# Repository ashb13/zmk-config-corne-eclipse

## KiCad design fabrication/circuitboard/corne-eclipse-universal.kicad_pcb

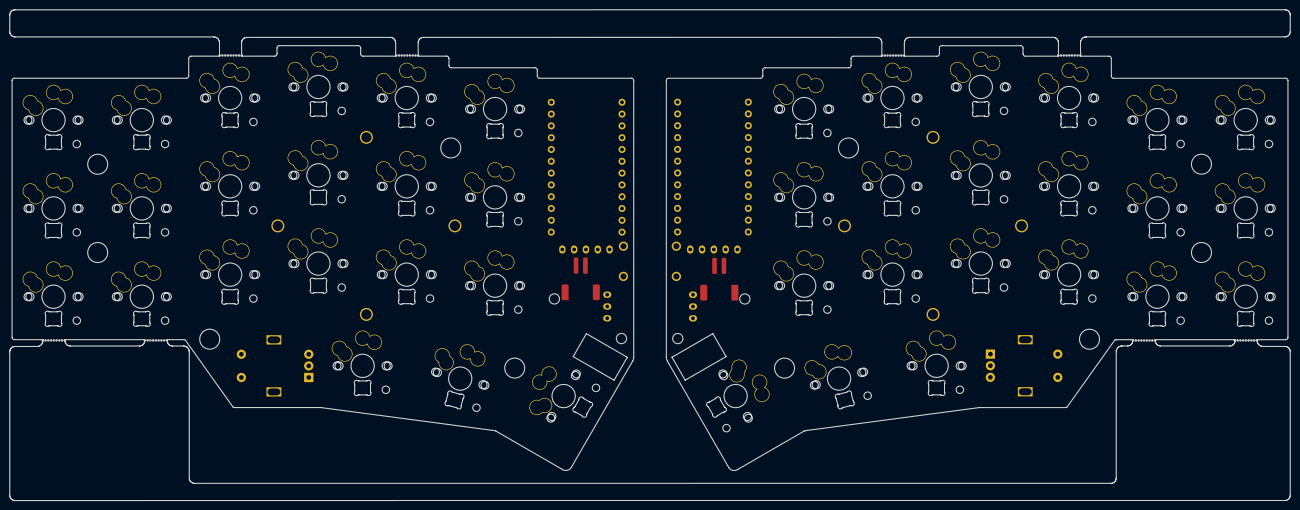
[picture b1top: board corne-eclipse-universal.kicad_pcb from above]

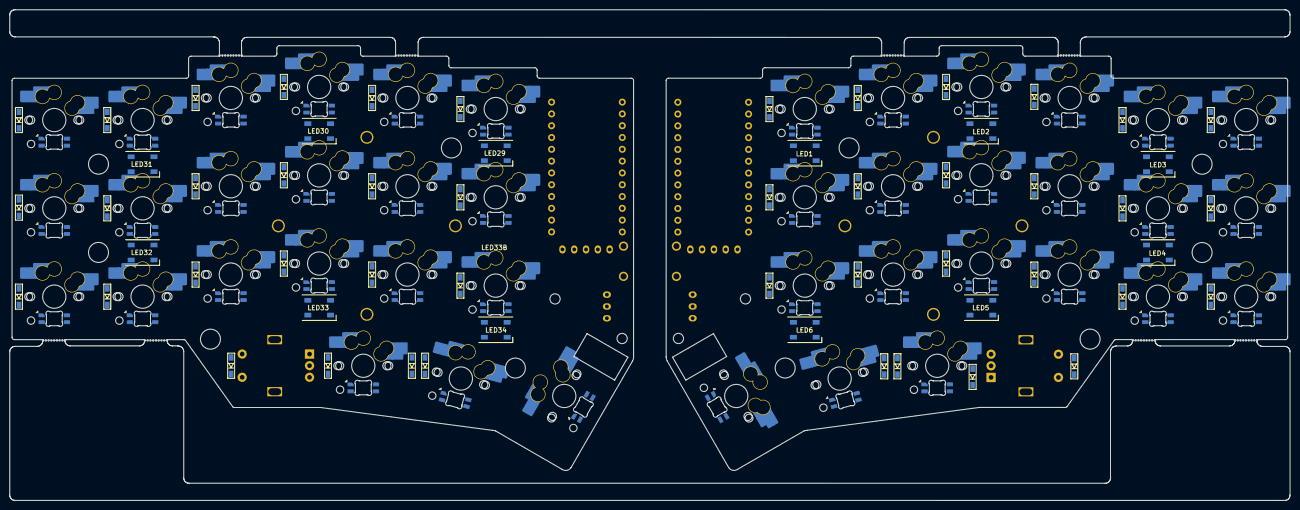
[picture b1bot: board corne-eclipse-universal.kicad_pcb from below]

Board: 2 copper layers, 275.5 x 105.6 mm, 178 parts (105 on the bottom side), 131 nets, no tracks yet.

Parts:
BT1, BT2, BT3, BT4, BT5, BT6, BT7, BT8: Breakaway_Tabs
D1, D2, D3, D4, D5, D6, D7, D8, D9, D10, D11, D12, D13, D14, D15, D16, D17, D18, D19, D19B, D20, D21, D22, D23, D24, D25, D26, D27, D28, D29, D30, D31, D32, D33, D34, D35, D36, D37, D38, D39, D40, D40B, D41, D42: D; D3_SMD_v2
ENC1, ENC2: RotaryEncoder_Alps_EC11E-Switch_Vertical_H20mm
J2, J4: OLED; nice!view
JPT1, JPT2: JST Passthrough
JST1, JST2: JST_PH_S2B-PH-SM4-TB_1x02-1MP_P2.00mm_Horizontal
LED1, LED2, LED3, LED4, LED5, LED6, LED29, LED30, LED31, LED32, LED33, LED33B: WS2812B; LED_WS2812B_PLCC4_5.0x5.0mm_P3.2mm
LED7, LED8, LED9, LED10, LED11, LED12, LED13, LED14, LED15, LED16, LED17, LED18, LED19, LED20, LED21, LED23, LED24, LED25, LED26, LED27, LED28, LED35, LED36, LED37, LED38, LED39, LED40, LED41, LED42, LED43, LED44, LED45, LED46, LED47, LED48, LED49, LED51, LED52, LED53, LED54, LED55, LED56: LED_6028R; LED_choc_6028R
MH1, MH2, MH3, MH4, MH5, MH6, MH7, MH8, MH9, MH10, MH11, MH12, MH13, MH14: Val**; M2_HOLE_v2
PWR1, PWR2: power
RSW1, RSW2: SW_PUSH; ResetSW_1side
SW1, SW2, SW3, SW4, SW5, SW6, SW7, SW8, SW9, SW10, SW11, SW12, SW13, SW14, SW15, SW16, SW17, SW18, SW20, SW21, SW23, SW24, SW25, SW26, SW27, SW28, SW29, SW30, SW31, SW32, SW33, SW34, SW35, SW36, SW37, SW38, SW39, SW40, SW42, SW43: SW_Universal_HS; SW_Universal_HS_1u
SW22, SW44: SW_Universal_HS; SW_Universal_HS_1.5u
TP1, TP2: Tenting Puck; Tenting_Puck
U1, U2: nice!nano; ProMicro_v3

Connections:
GND: ENC1.C, J2.4, LED1.3, LED2.3, LED3.3, LED4.3, LED5.3, LED6.3, LED7.2, LED8.2, LED9.2, LED10.2, LED11.2, LED12.2, LED13.2, LED14.2, LED15.2, LED16.2, LED17.2, LED18.2, LED19.2, LED20.2, LED21.2, LED23.2, LED24.2, LED25.2, LED26.2, LED27.2, LED28.2, U1.3, U1.4, U1.23
GNDA: ENC2.C, J4.4, LED29.3, LED30.3, LED31.3, LED32.3, LED33.3, LED33B.3, LED35.2, LED36.2, LED37.2, LED38.2, LED39.2, LED40.2, LED41.2, LED42.2, LED43.2, LED44.2, LED45.2, LED46.2, LED47.2, LED48.2, LED49.2, LED51.2, LED52.2, LED53.2, LED54.2, LED55.2, LED56.2, U2.3, U2.4, U2.23
LED_r: LED29.prev, U2.1
unnamed: D1.2, SW1.2
unnamed: D2.2, SW2.2
unnamed: D3.2, SW3.2
unnamed: D4.2, SW4.2
unnamed: D5.2, SW5.2
unnamed: D6.2, SW6.2
unnamed: D7.2, SW7.2
unnamed: D8.2, SW8.2
unnamed: D9.2, SW9.2
unnamed: D10.2, SW10.2
unnamed: D11.2, SW11.2
unnamed: D12.2, SW12.2
unnamed: D13.2, SW13.2
unnamed: D14.2, SW14.2
unnamed: D15.2, SW15.2
unnamed: D16.2, SW16.2
unnamed: D17.2, SW17.2
unnamed: D18.2, SW18.2
unnamed: D19B.2, ENC1.S1
unnamed: D19.2, SW20.2
unnamed: D20.2, SW21.2
unnamed: D21.2, SW22.2
unnamed: D22.2, SW23.2
unnamed: D23.2, SW24.2
unnamed: D24.2, SW25.2
unnamed: D25.2, SW26.2
unnamed: D26.2, SW27.2
unnamed: D27.2, SW28.2
unnamed: D28.2, SW29.2
unnamed: D29.2, SW30.2
unnamed: D30.2, SW31.2
unnamed: D31.2, SW32.2
unnamed: D32.2, SW33.2
unnamed: D33.2, SW34.2
unnamed: D34.2, SW35.2
unnamed: D35.2, SW36.2
unnamed: D36.2, SW37.2
unnamed: D37.2, SW38.2
unnamed: D38.2, SW39.2
unnamed: D39.2, SW40.2
unnamed: D40B.2, ENC2.S1
unnamed: D40.2, SW42.2
unnamed: D41.2, SW43.2
unnamed: D42.2, SW44.2
unnamed: ENC1.B, U1.11
unnamed: ENC1.A, U1.12
unnamed: ENC2.B, U2.11
unnamed: ENC2.A, U2.12
SCL: J2.2, U1.6
SCL_r: J4.2, U2.6
SDA: J2.1, U1.5
SDA_r: J4.1, U2.5
VCC: J2.3, LED1.1, LED2.1, LED3.1, LED4.1, LED5.1, LED6.1, LED7.3, LED8.3, LED9.3, LED10.3, LED11.3, LED12.3, LED13.3, LED14.3, LED15.3, LED16.3, LED17.3, LED18.3, LED19.3, LED20.3, LED21.3, LED23.3, LED24.3, LED25.3, LED26.3, LED27.3, LED28.3, U1.21
VDD: J4.3, LED29.1, LED30.1, LED31.1, LED32.1, LED33.1, LED33B.1, LED35.3, LED36.3, LED37.3, LED38.3, LED39.3, LED40.3, LED41.3, LED42.3, LED43.3, LED44.3, LED45.3, LED46.3, LED47.3, LED48.3, LED49.3, LED51.3, LED52.3, LED53.3, LED54.3, LED55.3, LED56.3, U2.21
col0: SW1.1, SW7.1, SW13.1, U1.20
col0_r: SW23.1, SW29.1, SW35.1, U2.20
col1: SW2.1, SW8.1, SW14.1, U1.19
col1_r: SW24.1, SW30.1, SW36.1, U2.19
col2: ENC1.S2, SW3.1, SW9.1, SW15.1, U1.18
col2_r: ENC2.S2, SW25.1, SW31.1, SW37.1, U2.18
col3: SW4.1, SW10.1, SW16.1, SW20.1, U1.17
col3_r: SW26.1, SW38.1, SW42.1, U2.17
col4: SW5.1, SW11.1, SW17.1, SW21.1, U1.16
col4_r: SW27.1, SW33.1, SW39.1, SW43.1, U2.16
col5: SW6.1, SW12.1, SW18.1, SW22.1, U1.15
col5_r: SW28.1, SW34.1, SW40.1, SW44.1, U2.15
data: J2.5, U1.2
data_r: J4.5, U2.2
led1-led2: LED1.next, LED2.prev
led2-led3: LED2.next, LED3.prev
led3-led4: LED3.next, LED4.prev
led4-led5: LED4.next, LED5.prev
led5-led6: LED5.next, LED6.prev
led6-led7: LED6.next, LED7.1
led7-led8: LED7.4, LED8.1
led8-led9: LED8.4, LED9.1
led9-led10: LED9.4, LED10.1
led10-led11: LED10.4, LED11.1
led11-led12: LED11.4, LED12.1
led12-led13: LED12.4, LED13.1
led13-led14: LED13.4, LED14.1
led14-led15: LED14.4, LED15.1
led15-led16: LED15.4, LED16.1
led16-led17: LED16.4, LED17.1
led17-led18: LED17.4, LED18.1
led18-led19: LED18.4, LED19.1
led19-led20: LED19.4, LED20.1
led20-led21: LED20.4, LED21.1
led21-led23: LED21.4, LED23.1
led23-led24: LED23.4, LED24.1
led24-led25: LED24.4, LED25.1
led25-led26: LED25.4, LED26.1
led26-led27: LED26.4, LED27.1
led27-led28: LED27.4, LED28.1
led29-led30: LED29.next, LED30.prev
led30-led31: LED30.next, LED31.prev
led31-led32: LED31.next, LED32.prev
led32-led33: LED32.next, LED33.prev
led33-led34: LED33.next, LED33B.prev
led34-led35: LED33B.next, LED35.1
led35-led36: LED35.4, LED36.1
led36-led37: LED36.4, LED37.1
led37-led38: LED37.4, LED38.1
led38-led39: LED38.4, LED39.1
led39-led40: LED39.4, LED40.1
led40-led41: LED40.4, LED41.1
led41-led42: LED41.4, LED42.1
led42-led43: LED42.4, LED43.1
led43-led44: LED43.4, LED44.1
led44-led45: LED44.4, LED45.1
led45-led46: LED45.4, LED46.1
led46-led47: LED46.4, LED47.1
led47-led48: LED47.4, LED48.1
led48-led49: LED48.4, LED49.1
led49-led51: LED49.4, LED51.1
led51-led52: LED51.4, LED52.1
led52-led53: LED52.4, LED53.1
led53-led54: LED53.4, LED54.1
led54-led55: LED54.4, LED55.1
led55-led56: LED55.4, LED56.1
row0: D1.1, D2.1, D3.1, D4.1, D5.1, D6.1, U1.7
row0_r: D22.1, D23.1, D24.1, D25.1, D26.1, D27.1, U2.7
row1: D7.1, D8.1, D9.1, D10.1, D11.1, D12.1, U1.8
row1_r: D28.1, D29.1, D30.1, D31.1, D32.1, D33.1, U2.8
row2: D13.1, D14.1, D15.1, D16.1, D17.1, D18.1, U1.9
row2_r: D34.1, D35.1, D36.1, D37.1, D38.1, D39.1, U2.9
row3: D19.1, D19B.1, D20.1, D21.1, U1.10
row3_r: D40.1, D40B.1, D41.1, D42.1, U2.10
